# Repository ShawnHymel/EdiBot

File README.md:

EdiBot
======

EdiBot is an object tracking robot. It looks for yellow objects in the field of vision of its webcam and attempts to drive toward the largest one. If the object takes up too much area in its field of view, EdiBot will back up.

Information on building and using EdiBot can be found on the [EdiBot 2.0 Hackster page](https://www.hackster.io/ShawnHymel/edibot-2-0-8ec2b0).

License Information
-------------------
The hardware is released under [Creative Commons Share-alike 4.0](https://creativecommons.org/licenses/by-sa/4.0/).
All other code is open source so please feel free to do anything you want with it; you buy me a beer if you use this and we meet someday ([Beerware license](http://en.wikipedia.org/wiki/Beerware)).

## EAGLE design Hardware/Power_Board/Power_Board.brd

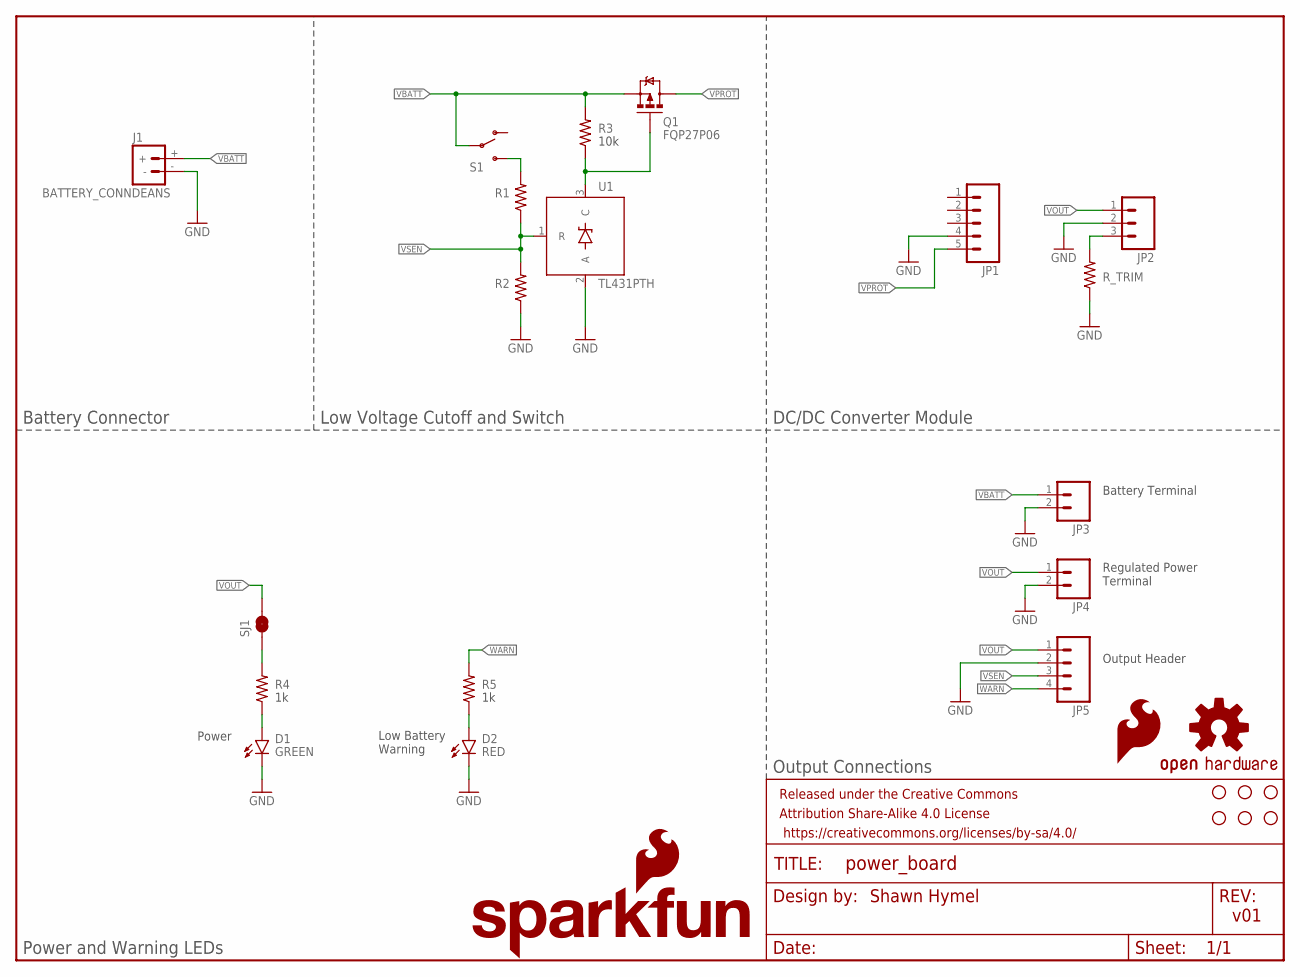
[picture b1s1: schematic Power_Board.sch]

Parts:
D1: GREEN; LED5MM
D2: RED; LED5MM
FRAME1: FRAME-LETTER; CREATIVE_COMMONS
J1: BATTERY_CONNDEANS; DEANS
JP1: M05LOCK; 1X05_LOCK
JP2: M03LOCK; 1X03_LOCK
JP3, JP4: M025MM; SCREWTERMINAL-5MM-2
JP5: M04LOCK; 1X04_LOCK
LOGO1: OSHW-LOGOS; OSHW-LOGO-S
LOGO2: SFE_LOGO_FLAME.1_INCH; SFE_LOGO_FLAME_.1
LOGO3: SFE_LOGO_NAME_FLAME.2_INCH; SFE_LOGO_NAME_FLAME_.2
Q1: MOSFET-PCHANNELFQP27P06; TO220V; PART_NAME FQP27P06
R1, R2, R3, R4, R5: RESISTORPTH-1/4W; AXIAL-0.4
R_TRIM: RESISTORPTH-1/4W; AXIAL-0.4
S1: SWITCH-SPDTPTH; SWITCH-SPDT
SJ1: JUMPER-PAD-2-NC_BY_TRACE; PAD-JUMPER-2-NC_BY_TRACE_YES_SILK
STANDOFF1, STANDOFF2, STANDOFF3, STANDOFF4, STANDOFF5, STANDOFF6: STAND-OFF
U1: TL431PTH; TO-92

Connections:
GND: D1.K (C), D2.K (C), J1.-, JP1.4, JP2.2, JP3.2, JP4.2, JP5.2, R2.P$1 (1), R_TRIM.P$1 (1), U1.2 (A)
unnamed: JP2.3, R_TRIM.P$2 (2)
unnamed: R1.P$2 (2), S1.3 (S)
unnamed: D1.A, R4.P$1 (1)
unnamed: D2.A, R5.P$1 (1)
unnamed: R4.P$2 (2), SJ1.1
unnamed: Q1.1 (G), R3.P$1 (1), U1.3 (C)
VBATT: J1.+, JP3.1, Q1.3 (S), R3.P$2 (2), S1.2
VOUT: JP2.1, JP4.1, JP5.1, SJ1.2
VPROT: JP1.5, Q1.2 (D)
VSEN: JP5.3, R1.P$1 (1), R2.P$2 (2), U1.1 (R)
WARN: JP5.4, R5.P$2 (2)

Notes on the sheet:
Battery Connector
Low Voltage Cutoff and Switch
DC/DC Converter Module
Power and Warning LEDs
Output Connections
Power
Low Battery Warning
Battery Terminal
Regulated Power Terminal
Output Header
10k

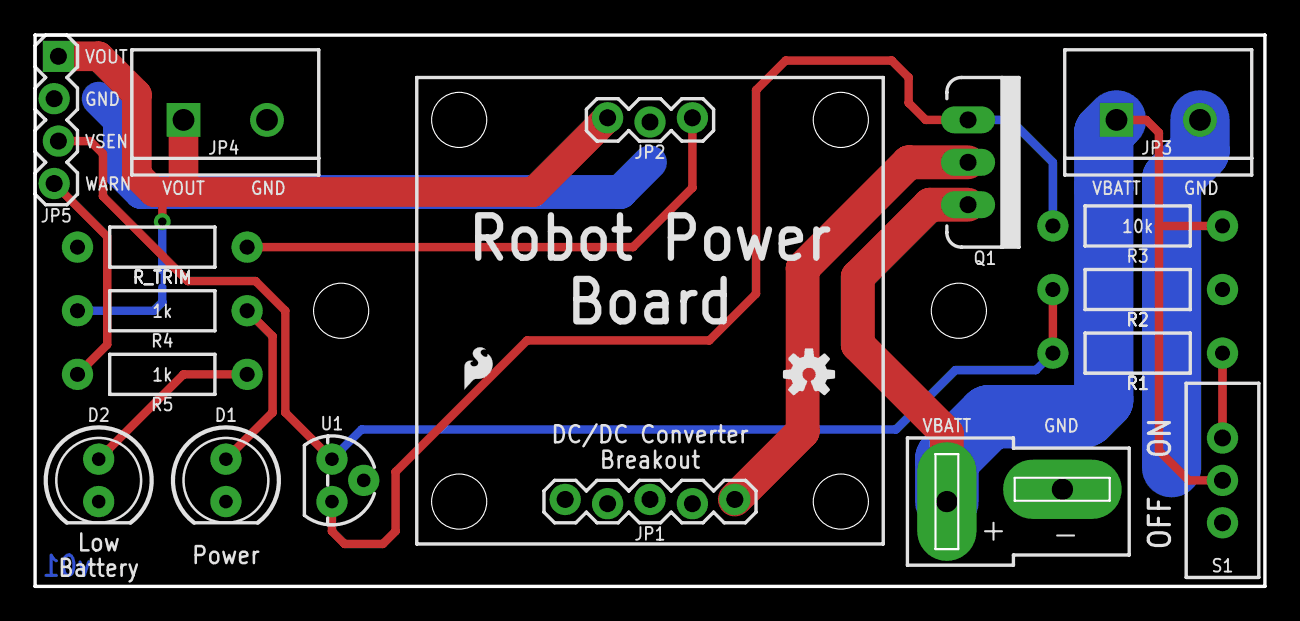
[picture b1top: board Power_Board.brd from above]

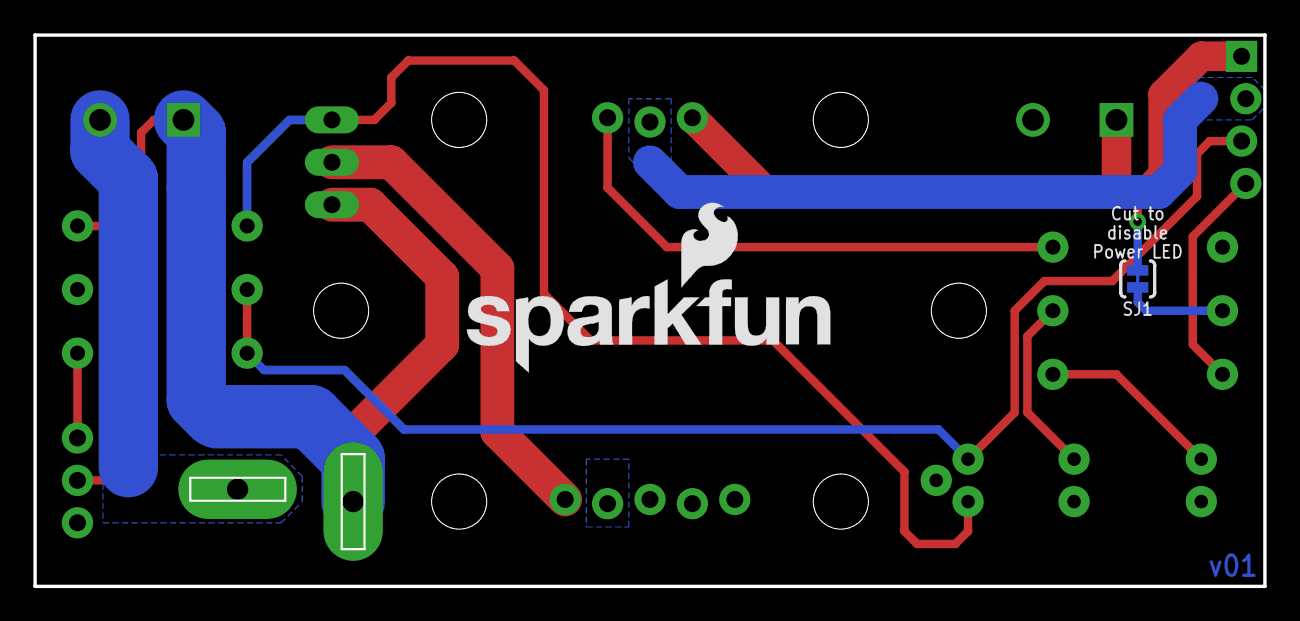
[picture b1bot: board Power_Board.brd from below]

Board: 2 copper layers, 73.7 x 33.0 mm, 28 parts (2 on the bottom side), 12 nets.

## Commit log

2015-02-25 Added beginning of ball chase, and working 'ball chase simple' script
2015-02-25 Added stop driving to whenever we see red but no circle
2015-02-25 Added sleep timer after each drive section.
2015-04-16 Finished power board layout.
2015-04-16 Added .gitignore file and removed temp files.
2015-04-16 Changed slot hits to Dimension layer and moved part names to outside parts.
2015-04-16 Added silk to solder/cut jumper on bottom.
2015-04-18 Created initial version of the firmataClient with digitalWrite and analogWrite
2015-04-20 Added analogRead to firmataClient
2015-04-21 First version of Ball Chase complete.
2015-04-21 Disabled debugging information.
2015-04-21 Added firmata reset to initialization of firmataClient.
2015-04-22 Added hack in firmataClient to reset Serial port. This *should* fix the issue where the firmata didn't work after a cold boot.
2015-04-24 Added low voltage warning LED.
2015-04-24 Changed camera line in lsusb to 'Logitech' when searching for a webcam.
2015-05-16 Changed MOSFET to FQP27P06.
2015-05-17 Added system architecture diagram.
2015-05-17 Added README and LICENSE files.
2015-05-17 Removed caption from image in README.
2015-05-24 Added Twitch Plays AVC script.
2015-06-11 Added push to start function
2015-06-12 Added push to start buttons
2015-06-13 Added keep-alive pongs.
2016-09-09 Initial commit for v2
2016-09-09 Fixed spin right
2016-09-13 Updated with smaller resolution, ability to turn off mraa, and swap motors.
2016-09-13 Use contour detection instead of blob detection to find objects
2016-09-14 Tweaked Ball Chase params
2016-09-15 Added chassis drawings
2016-09-16 Tweaked chase code. 3 sections instead of 5 per frame.
2016-09-16 Adjusted hue range for outdoors
2016-09-16 Updated readme. Again.

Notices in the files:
parts and their libraries:
SparkFun-LED: Licensing: Creative Commons ShareAlike 4.0 International - https://creativecommons.org/licenses/by-sa/4.0
SparkFun-Aesthetics: Released under the Creative Commons Attribution Share-Alike 4.0 License
SparkFun-Aesthetics: Released under the Creative Commons
